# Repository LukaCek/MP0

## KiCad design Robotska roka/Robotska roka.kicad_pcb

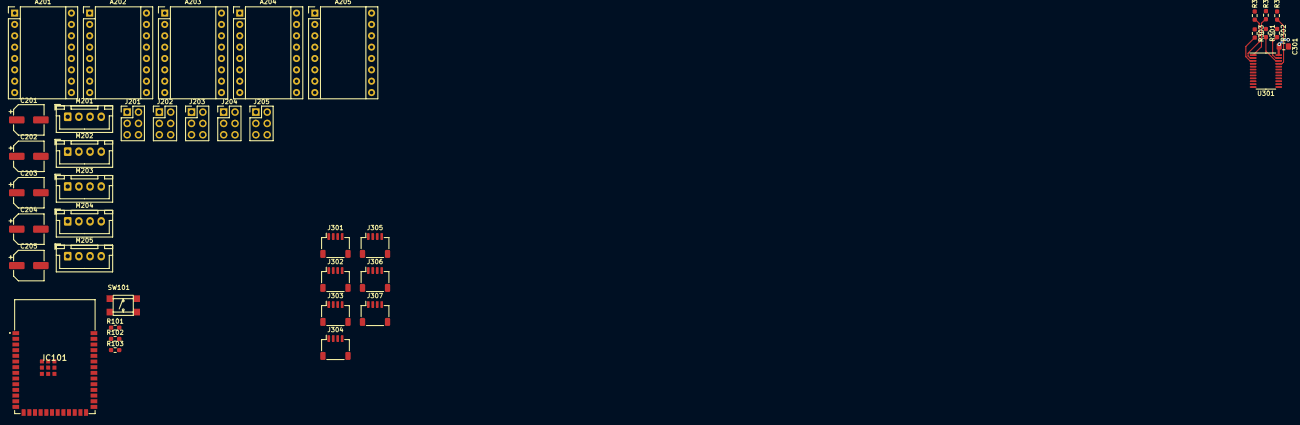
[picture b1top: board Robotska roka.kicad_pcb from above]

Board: 2 copper layers, 40 parts (0 on the bottom side), 74 nets.

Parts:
A201, A202, A203, A204, A205: Pololu_Breakout_DRV8825; Pololu_Breakout-16_15.2x20.3mm
C201, C202, C203, C204, C205: 100u; CP_Elec_6.3x7.7
C301: 10uF; C_0805_2012Metric_Pad1.18x1.45mm_HandSolder
IC101: ESP32-S3-WROOM-1-N4; ESP32S3WROOM1N4
J201, J202, J203, J204, J205: Conn_02x03_Counter_Clockwise; PinHeader_2x03_P2.54mm_Vertical
J301, J303, J304, J305, J306, J307: Conn_01x04_MountingPin; JST_SH_SM04B-SRSS-TB_1x04-1MP_P1.00mm_Horizontal
J302: MAIN; JST_SH_SM04B-SRSS-TB_1x04-1MP_P1.00mm_Horizontal
M201, M202, M203, M204, M205: MOTOR1; JST_XH_B4B-XH-A_1x04_P2.50mm_Vertical
R101, R102, R103, R301, R302, R303, R304, R305, R306: 10k; R_0603_1608Metric_Pad0.98x0.95mm_HandSolder
SW101: BOOT SW.; Tactile Sw... SHOU HAN TS4535TP 250gf 009
U301: TCA9548APWR; TSSOP-24_4.4x7.8mm_P0.65mm

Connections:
+3V3: C301.1, IC101.2 (3V3), J201.1, J201.3, J201.5, J202.1, J202.3, J202.5, J203.1, J203.3, J203.5, J204.1, J204.3, J204.5, J205.1, J205.3, J205.5, J301.2, J302.2, J303.2, J304.2, J305.2, J306.2, J307.2, R102.2, R301.1, R302.1, R303.1, U301.24 (VCC)
+24V: A201.8 (VMOT), A202.8 (VMOT), A203.8 (VMOT), A204.8 (VMOT), A205.8 (VMOT), C201.1, C202.1, C203.1, C204.1, C205.1
/I2C Sensors/SCL: IC101.17 (IO9), J302.4, R301.2, U301.22 (SCL)
/I2C Sensors/SDA: IC101.12 (IO8), J302.3, R302.2, U301.23 (SDA)
/Motors/DRV0 DIR: A201.16 (DIR), IC101.14 (IO20)
/Motors/DRV0 STEP: A201.15 (STEP), IC101.13 (IO19)
/Motors/DRV2 DIR: A204.16 (DIR), IC101.19 (IO11)
/Motors/DRV2 STEP: A204.15 (STEP), IC101.18 (IO10)
/Motors/DRV3 DIR: A205.16 (DIR), IC101.21 (IO13)
/Motors/DRV3 STEP: A205.15 (STEP), IC101.20 (IO12)
/Motors/DRV4 DIR: A202.16 (DIR), IC101.23 (IO21)
/Motors/DRV4 STEP: A202.15 (STEP), IC101.22 (IO14)
/Motors/DRV5 DIR: A203.16 (DIR), IC101.25 (IO48)
/Motors/DRV5 STEP: A203.15 (STEP), IC101.24 (IO47)
GND: A201.1 (GND), A201.7 (GND), A202.1 (GND), A202.7 (GND), A203.1 (GND), A203.7 (GND), A204.1 (GND), A204.7 (GND), A205.1 (GND), A205.7 (GND), C201.2, C202.2, C203.2, C204.2, C205.2, C301.2, IC101.1 (GND_1), IC101.40 (GND_2), IC101.41 (GND_3), IC101.42 (GND_4), IC101.43 (GND_5), IC101.44 (GND_6), IC101.45 (GND_7), IC101.46 (GND_8), IC101.47 (GND_9), IC101.48 (GND_10), IC101.49 (GND_11), J301.1, J301.MP (MountPin), J302.1, J302.MP (MountPin), J303.1, J303.MP (MountPin), J304.1, J304.MP (MountPin), J305.1, J305.MP (MountPin), J306.1, J306.MP (MountPin), J307.1, J307.MP (MountPin), R101.1, R103.1, R304.1, R305.1, R306.1, SW101.3 (K), SW101.4 (A), U301.12 (GND)
unnamed: A201.4 (A1), M201.2 (-)
unnamed: A201.3 (A2), M201.1
unnamed: A201.5 (B1), M201.3
unnamed: A201.6 (B2), M201.4
unnamed: A201.10 (M0), J201.6
unnamed: A201.11 (M1), J201.4
unnamed: A201.12 (M2), J201.2
unnamed: A201.13 (~RST), A201.14 (~SLP)
unnamed: A202.4 (A1), M202.2 (-)
unnamed: A202.3 (A2), M202.1
unnamed: A202.5 (B1), M202.3
unnamed: A202.6 (B2), M202.4
unnamed: A202.10 (M0), J202.6
unnamed: A202.11 (M1), J202.4
unnamed: A202.12 (M2), J202.2
unnamed: A202.13 (~RST), A202.14 (~SLP)
unnamed: A203.4 (A1), M203.2 (-)
unnamed: A203.3 (A2), M203.1
unnamed: A203.5 (B1), M203.3
unnamed: A203.6 (B2), M203.4
unnamed: A203.10 (M0), J203.6
unnamed: A203.11 (M1), J203.4
unnamed: A203.12 (M2), J203.2
unnamed: A203.13 (~RST), A203.14 (~SLP)
unnamed: A204.4 (A1), M204.2 (-)
unnamed: A204.3 (A2), M204.1
unnamed: A204.5 (B1), M204.3
unnamed: A204.6 (B2), M204.4
unnamed: A204.10 (M0), J204.6
unnamed: A204.11 (M1), J204.4
unnamed: A204.12 (M2), J204.2
unnamed: A204.13 (~RST), A204.14 (~SLP)
unnamed: A205.4 (A1), M205.2 (-)
unnamed: A205.3 (A2), M205.1
unnamed: A205.5 (B1), M205.3
unnamed: A205.6 (B2), M205.4
unnamed: A205.10 (M0), J205.6
unnamed: A205.11 (M1), J205.4
unnamed: A205.12 (M2), J205.2
unnamed: A205.13 (~RST), A205.14 (~SLP)
unnamed: IC101.27 (IO0), R102.1, SW101.1, SW101.2
unnamed: IC101.26 (IO45), R103.2
unnamed: IC101.16 (IO46), R101.2
unnamed: J301.3, U301.15 (SD5)
unnamed: J301.4, U301.16 (SC5)
unnamed: J303.3, U301.4 (SD0)
unnamed: J303.4, U301.5 (SC0)
unnamed: J304.3, U301.6 (SD1)
unnamed: J304.4, U301.7 (SC1)
unnamed: J305.3, U301.8 (SD2)
unnamed: J305.4, U301.9 (SC2)
unnamed: J306.3, U301.10 (SD3)
unnamed: J306.4, U301.11 (SC3)
unnamed: J307.3, U301.13 (SD4)
unnamed: J307.4, U301.14 (SC4)
unnamed: R306.2, U301.1 (A0)
unnamed: R305.2, U301.2 (A1)
unnamed: R304.2, U301.21 (A2)
unnamed: R303.2, U301.3 (~RESET)
